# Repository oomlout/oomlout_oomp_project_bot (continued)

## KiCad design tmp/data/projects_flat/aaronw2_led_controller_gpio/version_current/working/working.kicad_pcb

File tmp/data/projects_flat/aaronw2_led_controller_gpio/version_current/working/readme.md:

# led-controller-gpio by aaronw2  
This is a harvested standardized copy of a project from github.  
The original project can be found at:  
https://github.com/aaronw2/led-controller-gpio  
Please consult that link for additional, details, files, and license information.  
Note: It was auto harvested and if the original repo had more than one board file or anything out of the ordinary the files here are likely not representative.

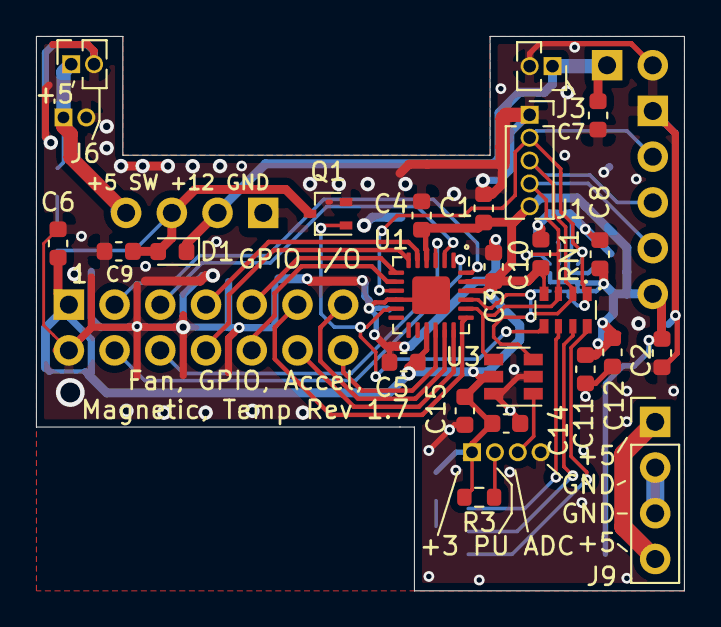
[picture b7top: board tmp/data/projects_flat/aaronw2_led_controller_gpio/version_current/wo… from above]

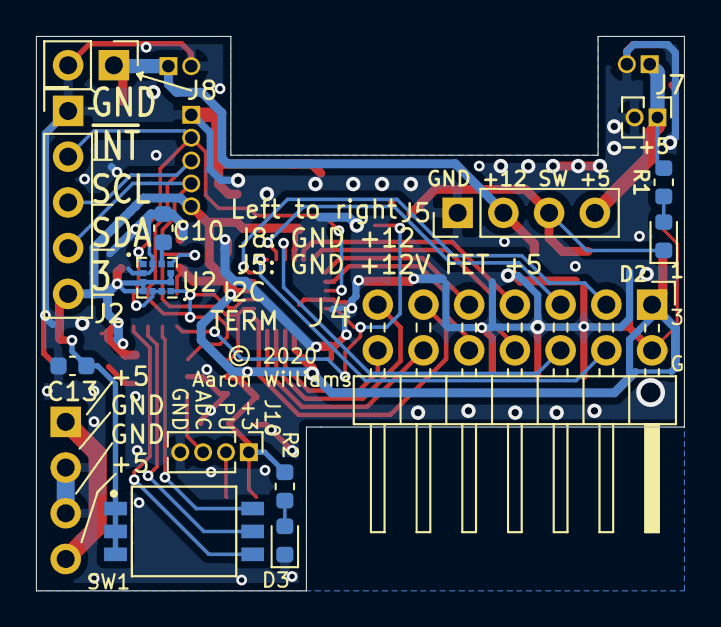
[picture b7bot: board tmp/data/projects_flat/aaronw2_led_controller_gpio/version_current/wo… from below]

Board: 2 copper layers, 36.0 x 30.8 mm, 38 parts (14 on the bottom side), 30 nets.

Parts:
C1, C2, C3, C4, C5, C6, C7, C9, C14: 1uF; C_0603_1608Metric
C8, C11, C13, C15: 0.1uF; C_0603_1608Metric
C10: 0.01uF; C_0603_1608Metric
C10#2: 0.22uF; C_0603_1608Metric
C12: 10uF; C_0603_1608Metric
D1: D_Schottky; D_0603_1608Metric
D2: LED RED; LED_0603_1608Metric
D3: LED GREEN; LED_0603_1608Metric
J1: Conn_01x05; PinSocket_1x05_P1.27mm_Vertical
J2: Conn_01x05 DNS; PinHeader_1x05_P2.54mm_Vertical
J3, J6: Conn_01x02; PinSocket_1x02_P1.27mm_Vertical
J4: Conn_02x07_Odd_Even; PinHeader_2x07_P2.54mm_Horizontal
J5, J9: Conn_01x04 DNS; PinHeader_1x04_P2.54mm_Vertical
J7: Conn_01x02 DNS; PinHeader_1x02_P1.27mm_Vertical
J8: Conn_01x02 DNS; PinHeader_1x02_P2.54mm_Vertical
J10: Conn_01x04 DNS; PinHeader_1x04_P1.27mm_Vertical
Q1: BSS214NW; SOT-323_SC-70
R1: 1K; R_0603_1608Metric
R2: 100; R_0603_1608Metric
R3: 4.7K; R_0603_1608Metric
RN1: 4.7K; R_Array_Convex_4x0603
SW1: SW_DIP_x03; SW_DIP_SPSTx03_Slide_Wurth_416131160803_8.89x4.98mm_W2.65mm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
U1: PCA9575HF; Texas_S-PVQFN-N24_EP2.1x2.1mm
U2: LSM303AGRTR; LGA-12_2x2mm_P0.5mm
U3: ADS1110; SOT-23-6

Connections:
+3V3: C1.1, C2.1, C3.1, C4.1, C5.1, C6.1, C8.1, C10.1, C11.1, C12.1, C13.1, C14.1, C15.1, J1.5, J2.5, J4.1, J10.1, R2.1, R3.1, RN1.4, SW1.1, SW1.2, SW1.3, U1.4, U1.15, U1.22, U1.23, U2.2, U2.3, U2.9, U2.10, U3.5
+5V: J5.4, J6.1, J7.1, R1.1
+12V: C7.1, D1.1, J3.1, J5.2, J8.1
/ADC_IN: J10.3, U3.1
/FAN_CTL: Q1.1, RN1.5, U1.11
/FET: C9.1, D1.2, D2.1, J5.3, Q1.3
/P0_0: J4.3, U1.24
/P0_1: J4.4, U1.1
/P0_2: J4.5, U1.2
/P0_3: J4.6, U1.3
/P0_4: J4.7, U1.5
/P0_5: J4.8, U1.6
/P0_6: J4.9, U1.7
/P0_7: J4.10, U1.8
/P1_0: J4.11, U1.19
/P1_1: J4.12, U1.18
/P1_2: J4.13, U1.17
/P1_3: J4.14, U1.16
/PU_OUT: J10.2, R3.2
/SCL: J1.3, J2.3, RN1.2, U1.21, U2.1, U3.3
/SCL_PU: RN1.6, SW1.6
/SDA: J1.4, J2.4, RN1.3, U1.20, U2.4, U3.4
/SDA_PU: RN1.7, SW1.5
/~INT: J1.2, J2.2, RN1.1, U1.9, U2.7, U2.11, U2.12
/~INT_PU: RN1.8, SW1.4
GND: C1.2, C2.2, C3.2, C4.2, C5.2, C6.2, C7.2, C8.2, C9.2, C10.2, C10#2.2, C11.2, C12.2, C13.2, C14.2, C15.2, D3.1, J1.1, J2.1, J3.2, J4.2, J5.1, J6.2, J7.2, J8.2, J9.2, J9.3, J10.4, Q1.2, U1.10, U1.25, U2.6, U2.8, U3.2, U3.6
unnamed: C10#2.1, U2.5
unnamed: D2.2, R1.2
unnamed: D3.2, R2.2
unnamed: J9.1, J9.4

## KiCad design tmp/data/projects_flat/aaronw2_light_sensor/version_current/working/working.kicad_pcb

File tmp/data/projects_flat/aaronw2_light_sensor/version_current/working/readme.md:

# light-sensor by aaronw2  
This is a harvested standardized copy of a project from github.  
The original project can be found at:  
https://github.com/aaronw2/light-sensor  
Please consult that link for additional, details, files, and license information.  
Note: It was auto harvested and if the original repo had more than one board file or anything out of the ordinary the files here are likely not representative.

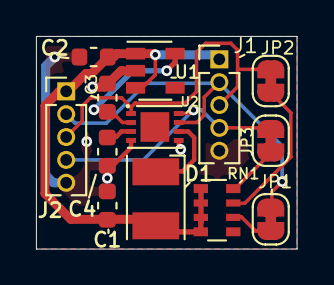
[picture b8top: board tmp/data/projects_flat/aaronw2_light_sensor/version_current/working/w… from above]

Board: 2 copper layers, 14.5 x 11.8 mm, 13 parts (0 on the bottom side), 11 nets.

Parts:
C1, C2, C3, C4: 1uF; C_0603_1608Metric
D1: VSMY3940X01-GS08; LED_PLCC-2
J1, J2: Conn_01x05; PinHeader_1x05_P1.27mm_Vertical
JP1, JP2, JP3: SolderJumper_2_Bridged; SolderJumper-2_P1.3mm_Bridged_RoundedPad1.0x1.5mm
RN1: 10K; R_Array_Convex_4x0603
U1: TLV71318PDBV; SOT-23-5
U2: ADUX1020; LFCSP-8-1EP_3x2mm_P0.5mm_EP1.6x1.65mm

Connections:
+3V3: C1.1, C2.1, D1.2, J1.1, J2.1, RN1.5, RN1.6, RN1.7, RN1.8, U1.1, U1.3
/1.8V: C3.1, U1.5, U2.2
/LEDX: D1.1, U2.6
/SCL: J1.3, J2.3, JP2.1, U2.1
/SDA: J1.4, J2.4, JP3.1, U2.8
/VREF: C4.1, U2.3
/~INT: J1.2, J2.2, JP1.1, U2.7
GND: C1.2, C2.2, C3.2, C4.2, J1.5, J2.5, U1.2, U2.4, U2.5
unnamed: JP1.2, RN1.2
unnamed: JP2.2, RN1.3
unnamed: JP3.2, RN1.4
